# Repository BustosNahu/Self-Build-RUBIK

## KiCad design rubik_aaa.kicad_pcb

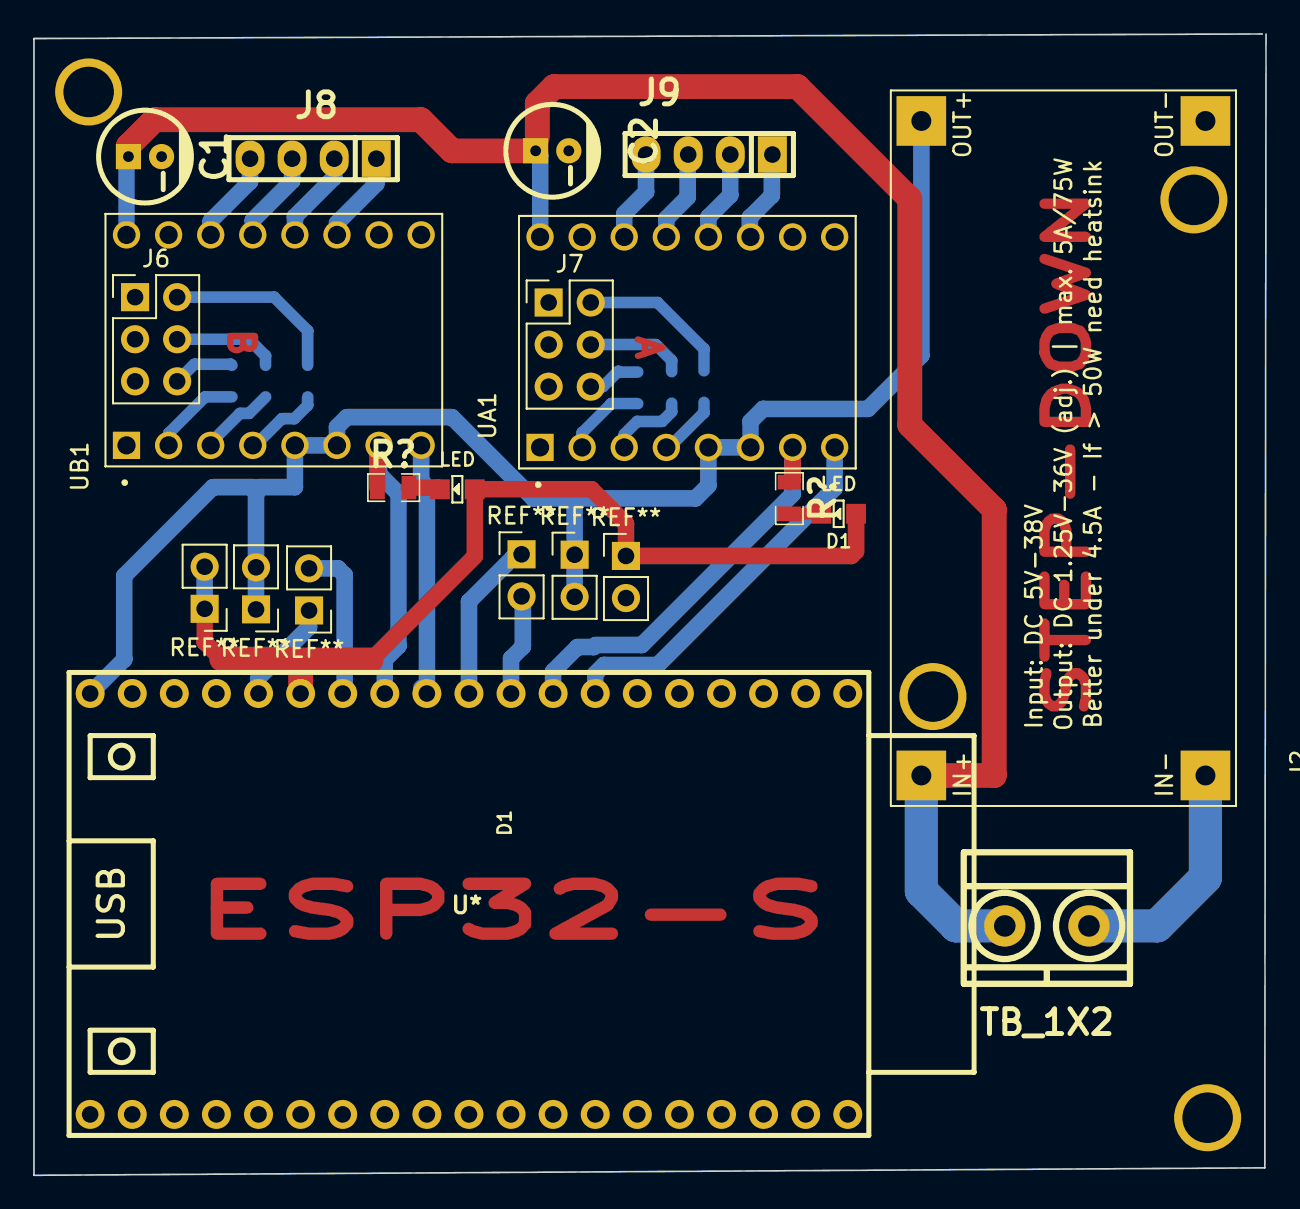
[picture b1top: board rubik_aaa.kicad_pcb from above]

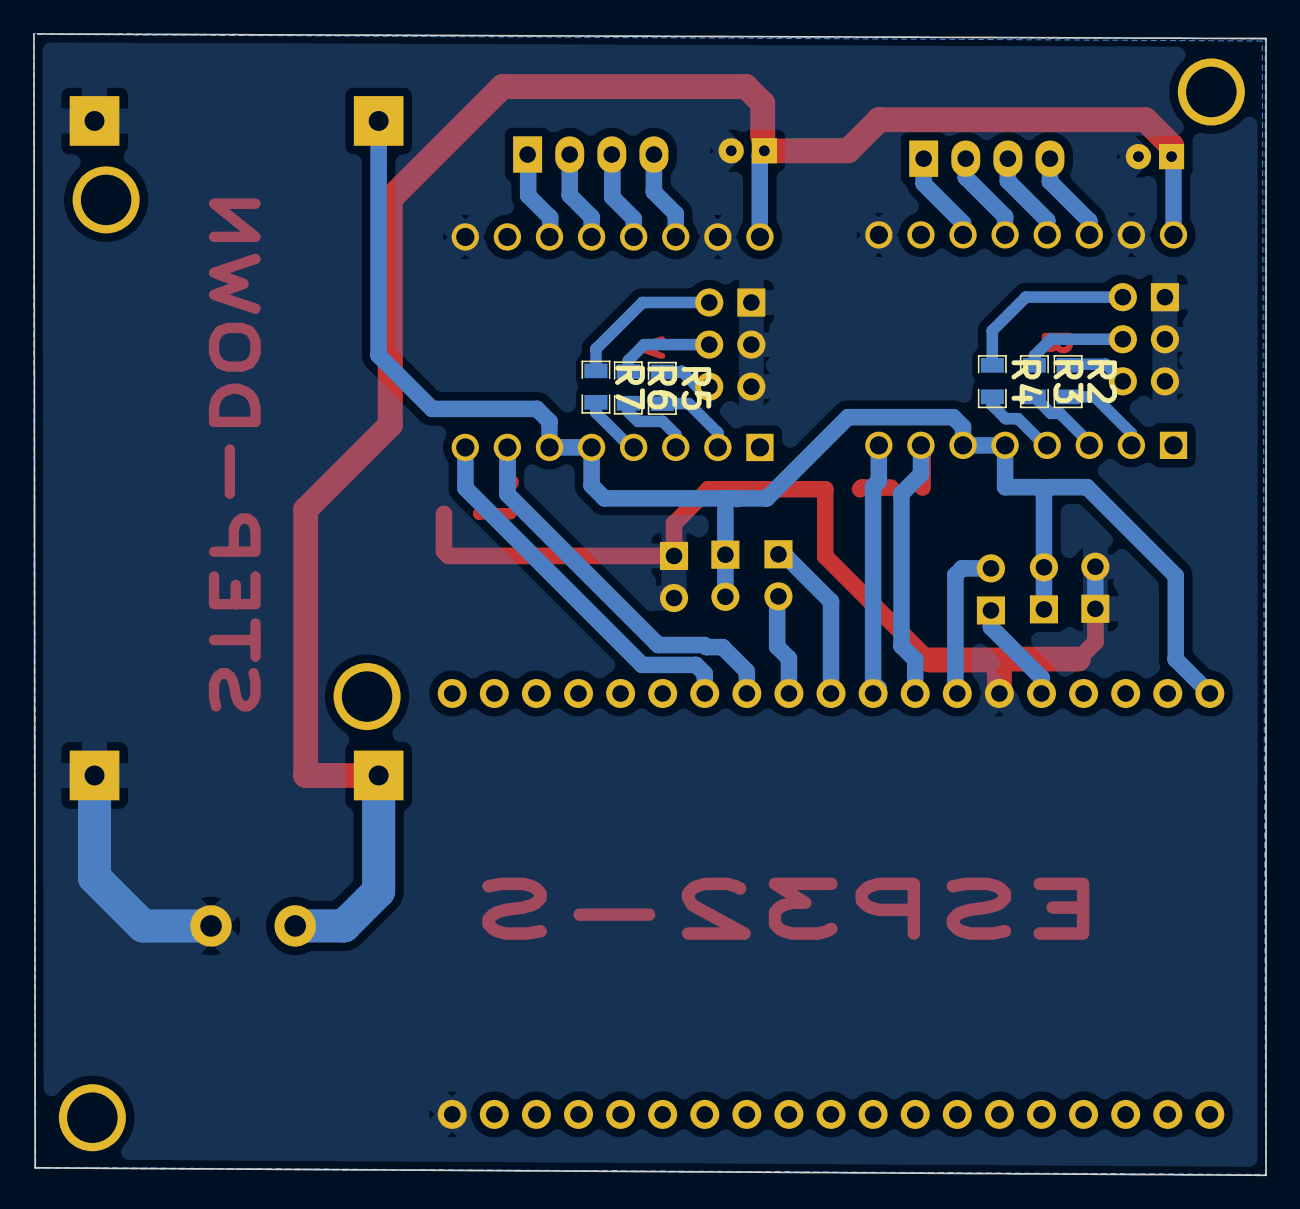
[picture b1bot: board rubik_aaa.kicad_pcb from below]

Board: 2 copper layers, 74.3 x 68.9 mm, 21 parts (6 on the bottom side), 28 nets.

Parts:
C1, C2: CAPAPOL; CAP_ELEC_5x11mm
D1, D1#2: LED; Led_0805
J1: TB_1X2; BORNERA2_AZUL
J2: Step_Down_Mini; XL4005_DC-DC
J6, J7: HEADER_3x2; PinHeader_2x03_P2.54mm_Vertical
J8, J9: HEADER_4; pin_strip_4
R2, R3, R4, R5, R6, R7: 10k; R_0805
R?: Value; R_0805
R?#2: Value; R_0805
U*: ESP32_DEVKITC
UA1: DRV8825_STEPPER_MOTOR_DRIVER_CARRIER; IC_DRV8825_STEPPER_MOTOR_DRIVER_CARRIER
UB1: DRV8825_STEPPER_MOTOR_DRIVER_CARRIER; IC_DRV8825_STEPPER_MOTOR_DRIVER_CARRIER

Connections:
5v: J2.3, U*.19, UA1.5 (~RST), UA1.6 (~SLP), UB1.5 (~RST), UB1.6 (~SLP)
12V: C1.1, C2.1, J1.1, J2.1, UA1.16 (VMOT), UB1.16 (VMOT)
/11A: J8.1, UB1.11 (A2)
/11C: J9.1, UA1.11 (A2)
/12A: J8.2, UB1.12 (A1)
/12C: J9.2, UA1.12 (A1)
/DIR_A: U*.7, UA1.8 (DIR)
/DIR_B: U*.11, UB1.8 (DIR)
/STEP_A: R?#2.1, U*.8, UA1.7 (STEP)
/STEP_B: R?.1, U*.12, UB1.7 (STEP)
GND: C1.2, C2.2, D1.1 (K), D1#2.1 (K), J1.2, J2.2, J2.4, J6.1, J6.3, J6.5, J7.1, J7.3, J7.5, U*.14, U*.38, UA1.9 (GND), UA1.15 (GND_MOT), UB1.9 (GND), UB1.15 (GND_MOT)
unnamed: J6.2, R4.1
unnamed: J6.4, R3.1
unnamed: J6.6, R2.1
unnamed: J7.2, R7.1
unnamed: J7.4, R6.1
unnamed: J7.6, R5.1
unnamed: R5.2, UA1.2 (M0)
unnamed: R6.2, UA1.3 (M1)
unnamed: R7.2, UA1.4 (M2)
unnamed: J9.3, UA1.13 (B1)
unnamed: J9.4, UA1.14 (B2)
unnamed: R2.2, UB1.2 (M0)
unnamed: R3.2, UB1.3 (M1)
unnamed: R4.2, UB1.4 (M2)
unnamed: J8.3, UB1.13 (B1)
unnamed: J8.4, UB1.14 (B2)
led_res_2: D1.2 (A), R?.2

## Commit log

2022-08-09 version 1.0.0
2022-10-31 actualizado
2023-08-09 v2.0
2023-08-09 Add files via upload
    funtional version
